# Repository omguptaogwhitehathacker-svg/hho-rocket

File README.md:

<h1>This project consists of four primary systems to give an rocket that burns fuel made from water. they are:</h1>
<h3> 1. the fuel generator:</h3>
it is a wet cell electrolysis chamber which has 12 carbon rods submerged in a NOAH solution with water, the carbon rods work as electrodes with minimal decay to produce a mixture of hydrogen gas and oxygen gas from water. It has a water inlet a one-way valved gas outlet and a simple wire system connecting the carbon rods with alternating polarity. This particular version of the hho generator uses 3.3v at 35a to give the best result with minimal decay, the power is provided externally from a circuit controlling this generator.
<h3>2. The main rocket:</h3>
This rocket model is made up of pure stainless steel and is water cooled from another ss tube surrounding it, to ensure the rocket body does not melt a high-power pump along with a water-cooling brick and fan is used to cool the water. There are two ignition carbon rods inserted into the main rocket body to deliver high current sparks for ignition these are insulated from the rest of the body to prevent mishaps.
The rocket nozzle is inspired from real life NASA designs with a converging and then diverging design to deliver maximum boost.
<h3>3. The brain:</h3>
Since this is an very dangerous project including th e production and combustion of hydrogen to safeguard this procedure and to control and monitor the functioning of this project an custom circuit with an ESP32-S3 and multiple relays and temprature sensors ensure the proper functioning of this project and even shuts it down in case of emergencies. This circuit uses an oled an esp32 32 relays and an external power supply for its functioning, It can also be activated wirelessly to ensure proper safety of the user.

<h3>4. The gas storage:</h3>
Since the hho generator doesnt actually produce enough gas to br directly used in the rocket an low pressure gas storage can is used at a minimum pressure of 10psi.

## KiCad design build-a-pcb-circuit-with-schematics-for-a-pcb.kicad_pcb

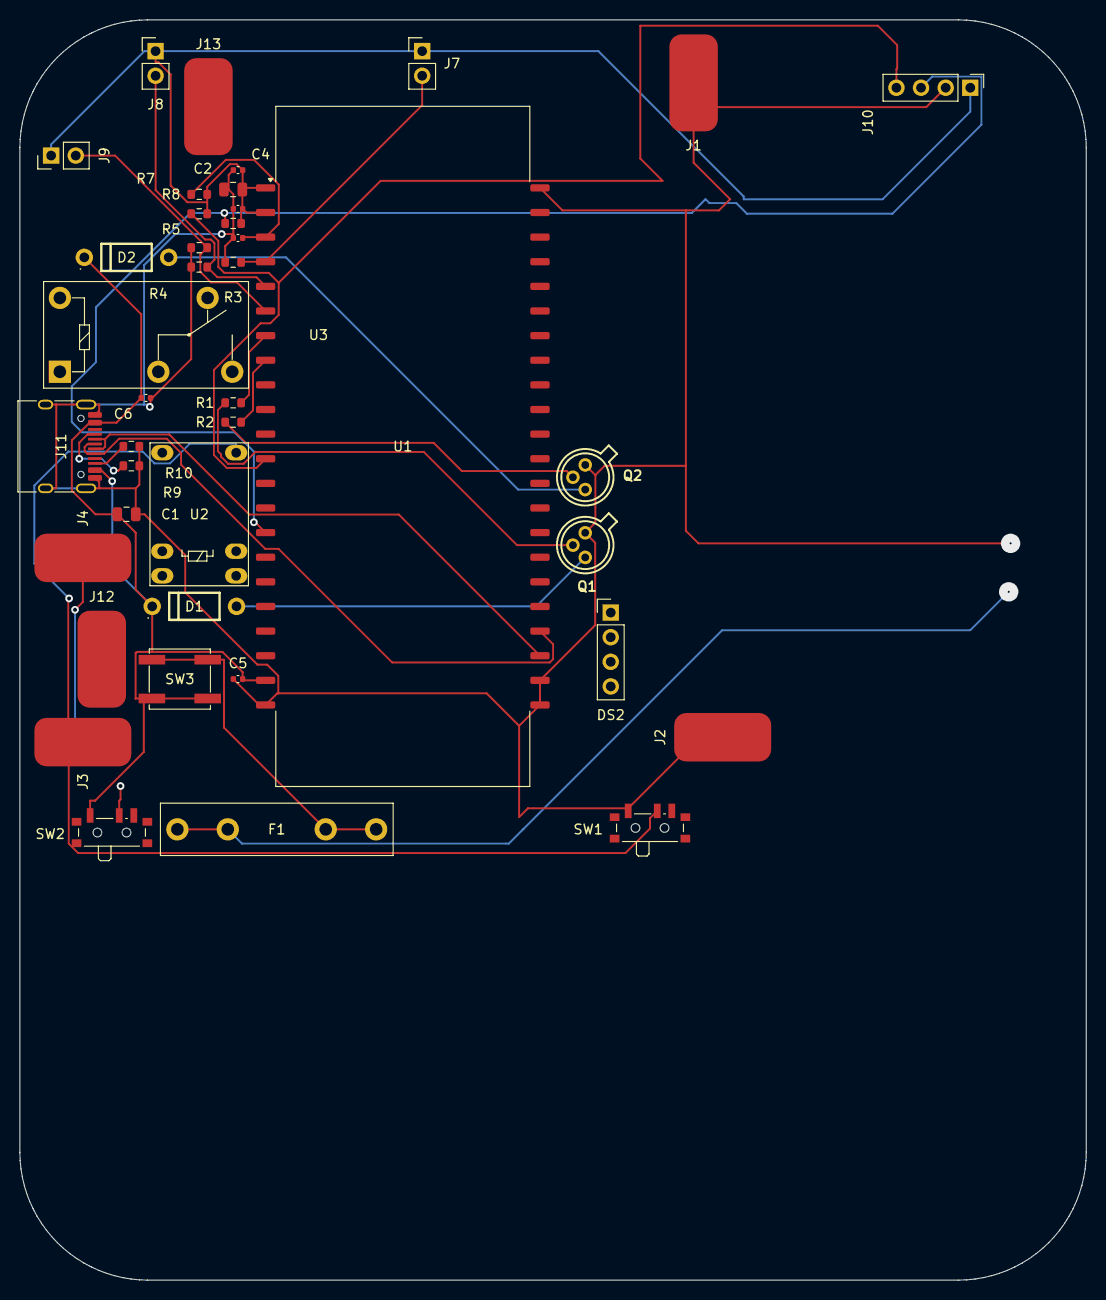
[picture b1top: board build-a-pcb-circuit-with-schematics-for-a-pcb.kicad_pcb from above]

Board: 2 copper layers, 110.0 x 130.0 mm, 40 parts (0 on the bottom side), 22 nets.

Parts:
C1, C2: 10uF; C_0805_2012Metric
C3, C4, C5, C6, C7: 100nF; C_0402_1005Metric
D1, D2: 1N4007; DO-41_BD2.4-L4.7-P8.70-D0.9-RD
DS2: OLED 1.3in SSD1306 I2C (GND,VCC,SCL,SDA); PinHeader_1x04_P2.54mm_Vertical
F1: 5A fuse; Fuseholder_Littelfuse_445_030_series_5x20mm
J1: HHO PSU pad, +35A feed into relay U2; SolderWirePad_1x01_SMD_5x10mm
J2: HHO PSU pad, power ground return; SolderWirePad_1x01_SMD_5x10mm
J3: HHO REACTOR 3.3V 35A; SolderWirePad_1x01_SMD_5x10mm
J4: ROCKET IGNITION 5V SOLDER PAD; SolderWirePad_1x01_SMD_5x10mm
J7: THERMISTOR HHO BODY; PinHeader_1x02_P2.54mm_Vertical
J8: THERMISTOR ROCKET NOZZLE; PinHeader_1x02_P2.54mm_Vertical
J9: THERMISTOR ROCKET BODY; PinHeader_1x02_P2.54mm_Vertical
J10: OLED I2C; PinHeader_1x04_P2.54mm_Vertical
J11: USB-C receptacle (native USB-Serial-JTAG programm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; USB_C_Receptacle_HRO_TYPE-C-31-M-12
J12: IGNITION GND SOLDER PAD; SolderWirePad_1x01_SMD_5x10mm
J13: HHO GND SOLDER PAD; SolderWirePad_1x01_SMD_5x10mm
Q1, Q2: 2N2222; TO-18
R1, R2: 1k; R_0603_1608Metric
R3, R4, R5, R8: 10k; R_0603_1608Metric
R6, R7: 4.7k; R_0603_1608Metric
R9, R10: 5.1k; R_0603_1608Metric
SW1: SPDT heavy-duty toggle 20A; SW_SPDT_PCM12
SW2: IGN_SWITCH; SW_SPDT_PCM12
SW3: SPST master toggle 10A; SW_SPST_EVPBF
U1: ESP32-S3-DevKitC-1 N16R8; ESP32_S3_DevKitC1_SYMBOL_BRIDGE
U2: G5LE-1 5V relay; Relay_SPDT_HJR-4102
U3: G5LE-1 5V relay; Relay_SPDT_Omron-G5Q-1

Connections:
+3V3: C2.1, C3.1, C4.1, J7.1, J8.1, J9.1, J10.1, R6.1, R7.1, R8.1, U1.1, U1.2
+5V: C1.1, C5.1, C6.1, D1.1, D2.1, J11.A4, J11.A9, J11.B4, J11.B9, SW2.1, SW3.2, U1.21
ADC_BODY: J9.2, R5.1, U1.6
ADC_HHO: J7.2, R3.1, U1.4
ADC_NOZ: J8.2, R4.1, U1.5
BASE1: Q1.2, R1.2
BASE2: Q2.2, R2.2
CC1: J11.A5, R9.1
CC2: J11.B5, R10.1
COIL1: D1.2, Q1.3
COIL2: D2.2, Q2.3
EN: C7.1, R8.2, U1.3
GND: C1.2, C2.2, C3.2, C4.2, C5.2, C6.2, C7.2, J1.1, J2.1, J10.2, J11.A1, J11.A12, J11.B1, J11.B12, J11.SH, J12.1, J13.1, Q1.1, Q2.1, R3.2, R4.2, R5.2, R9.2, R10.2, SW1.1, U1.22, U1.23, U1.24, U1.44
HHO_OUT: J3.1, SW1.2, U2.12
I2C_SCL: J10.3, R6.2, U1.15
I2C_SDA: J10.4, R7.2, U1.12
IGN_OUT: J4.1, SW2.2
RELAY1_CTRL: R1.1, U1.7
RELAY2_CTRL: R2.1, U1.8
USB_D+: J11.A6, J11.B6, U1.26
USB_D-: J11.A7, J11.B7, U1.25
VIN_FUSED: F1.2, SW3.1
